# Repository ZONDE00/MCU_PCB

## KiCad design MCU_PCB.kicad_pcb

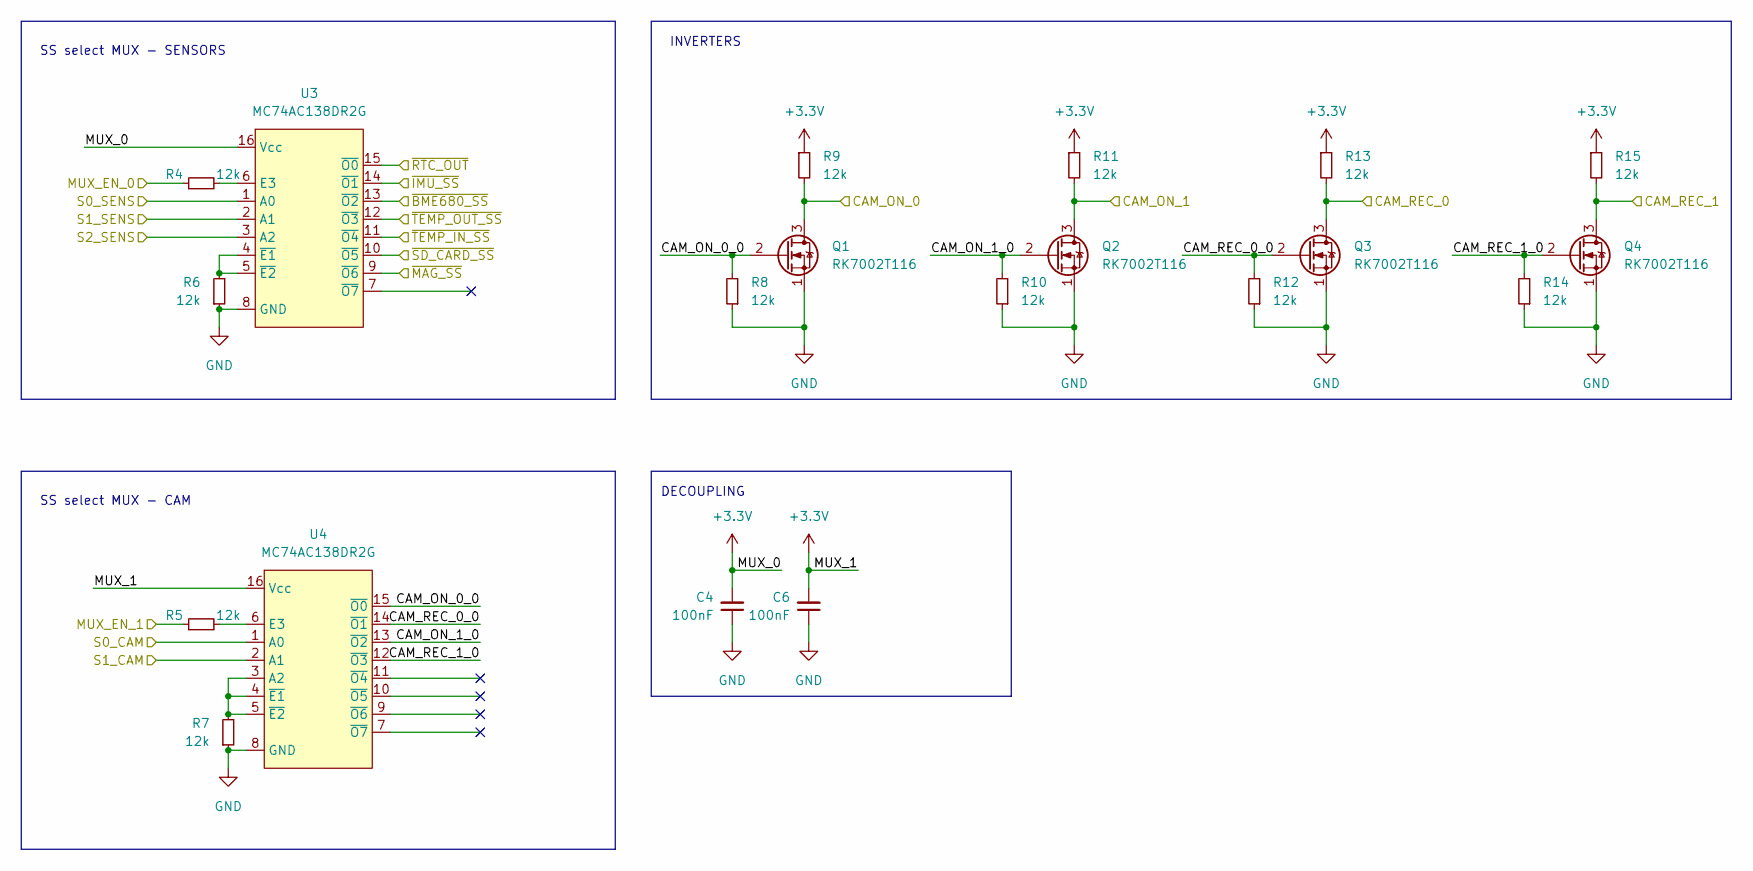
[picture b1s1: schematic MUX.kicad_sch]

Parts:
C4, C6: 100nF; C_0402_1005Metric
Q1, Q2, Q3, Q4: RK7002T116; SOT-23
R4, R5, R6, R7, R8, R9, R10, R11, R12, R13, R14, R15: 12k; R_0402_1005Metric
U3, U4: MC74AC138DR2G; SOIC-16_3.9x9.9mm_P1.27mm

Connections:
+3V3: C4.2, C6.2, R9.1, R11.1, R13.1, R15.1, U3.16 (Vcc), U4.16 (Vcc); also elsewhere on the board
/CAM_SENS/ON/OFF_0: Q1.3 (D), R9.2; also elsewhere on the board
/CAM_SENS/ON/OFF_1: Q2.3 (D), R11.2; also elsewhere on the board
/CAM_SENS/REC_0: Q3.3 (D), R13.2; also elsewhere on the board
/CAM_SENS/REC_1: Q4.3 (D), R15.2; also elsewhere on the board
/CAM_SENS/~BME680_SS: U3.13 (~O2); also elsewhere on the board
/CAM_SENS/~TEMP_OUT_SS: U3.12 (~O3); also elsewhere on the board
/MCU/MUX_EN_0: R4.1; also elsewhere on the board
/MCU/MUX_EN_1: R5.1; also elsewhere on the board
/MCU/S0_CAM: U4.1 (A0); also elsewhere on the board
/MCU/S0_SENS: U3.1 (A0); also elsewhere on the board
/MCU/S1_CAM: U4.2 (A1); also elsewhere on the board
/MCU/S1_SENS: U3.2 (A1); also elsewhere on the board
/MCU/S2_SENS: U3.3 (A2); also elsewhere on the board
/MUX/CAM_ON_0_0: Q1.2 (G), R8.2, U4.15 (~O0)
/MUX/CAM_ON_1_0: Q2.2 (G), R10.2, U4.13 (~O2)
/MUX/CAM_REC_0_0: Q3.2 (G), R12.2, U4.14 (~O1)
/MUX/CAM_REC_1_0: Q4.2 (G), R14.2, U4.12 (~O3)
/MUX/~IMU_SS: U3.14 (~O1); also elsewhere on the board
/MUX/~MAG_SS: U3.9 (~O6); also elsewhere on the board
/MUX/~RTC_OUT: U3.15 (~O0); also elsewhere on the board
/MUX/~SD_CARD_SS: U3.10 (~O5); also elsewhere on the board
/MUX/~TEMP_IN_SS: U3.11 (~O4); also elsewhere on the board
GND: C4.1, C6.1, Q1.1 (S), Q2.1 (S), Q3.1 (S), Q4.1 (S), R6.1, R7.1, R8.1, R10.1, R12.1, R14.1, U3.8 (GND), U4.8 (GND); also elsewhere on the board
unnamed: R4.2, U3.6 (E3)
unnamed: R5.2, U4.6 (E3)
unnamed: R6.2, U3.4 (~E1), U3.5 (~E2)
unnamed: R7.2, U4.3 (A2), U4.4 (~E1), U4.5 (~E2)

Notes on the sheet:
SS select MUX - SENSORS
SS select MUX - CAM
INVERTERS
DECOUPLING

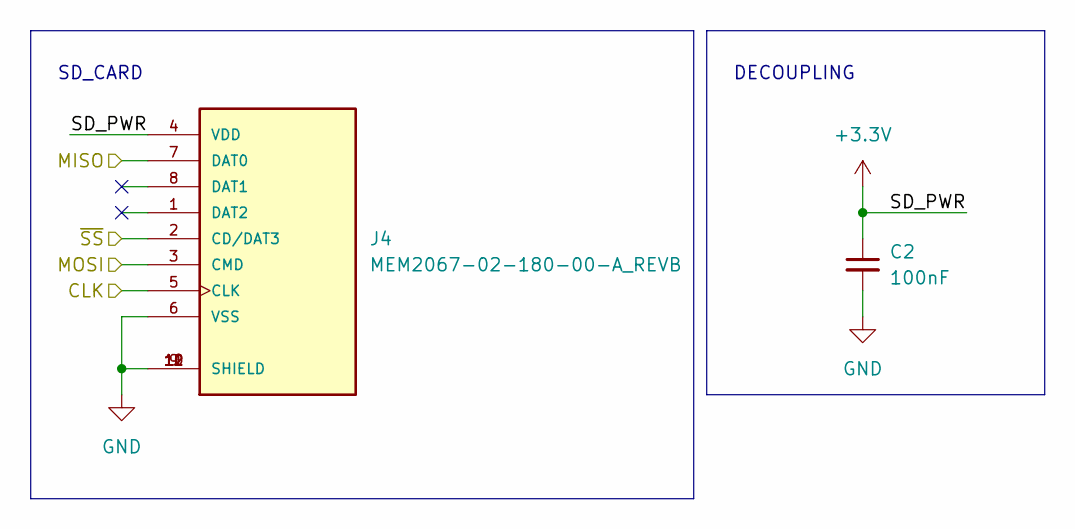
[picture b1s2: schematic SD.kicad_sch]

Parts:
C2: 100nF; C_0402_1005Metric
J4: MEM2067-02-180-00-A_REVB; GCT_MEM2067-02-180-00-A_REVB

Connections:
+3V3: C2.1, J4.4 (VDD); also elsewhere on the board
/CAM_SENS/CLK: J4.5 (CLK); also elsewhere on the board
/CAM_SENS/MISO: J4.7 (DAT0); also elsewhere on the board
/CAM_SENS/MOSI: J4.3 (CMD); also elsewhere on the board
/MUX/~SD_CARD_SS: J4.2 (CD/DAT3); also elsewhere on the board
GND: C2.2, J4.6 (VSS), J4.9 (SHIELD), J4.10 (SHIELD), J4.11 (SHIELD), J4.12 (SHIELD); also elsewhere on the board

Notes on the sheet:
SD_CARD
DECOUPLING

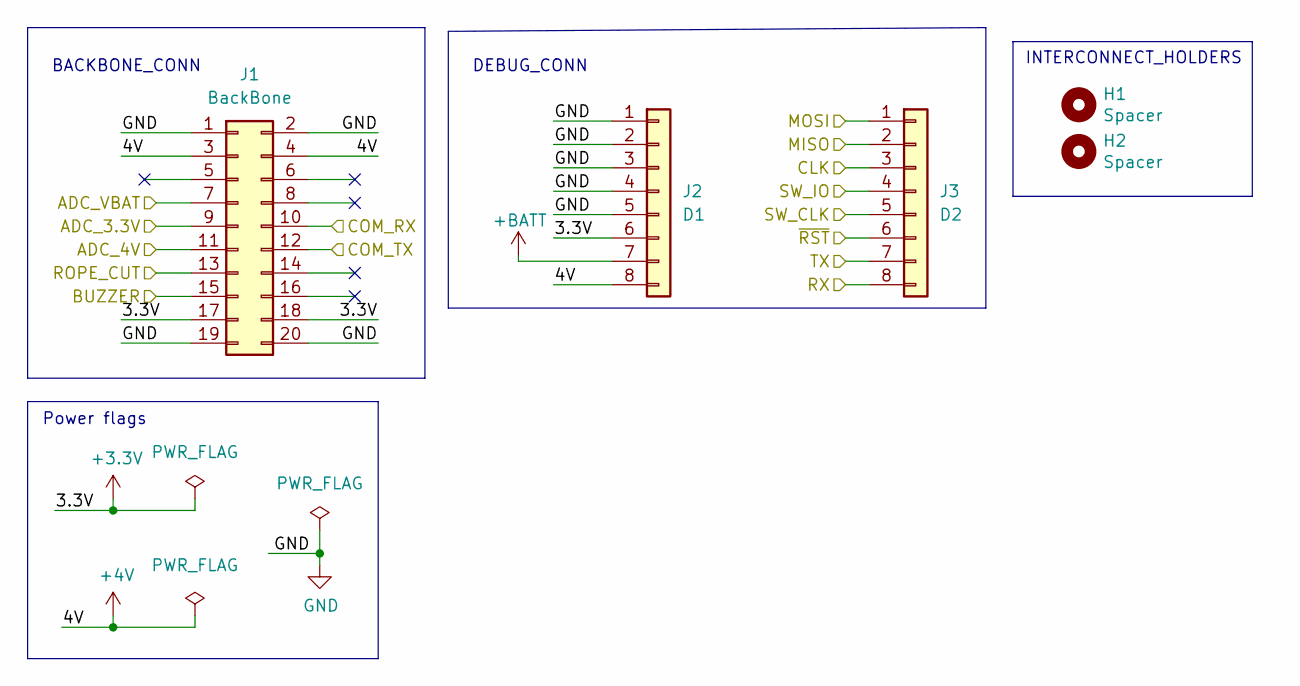
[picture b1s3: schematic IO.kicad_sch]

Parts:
H1, H2: Spacer; MountingHole_3.2mm_M3
J1: BackBone; PinSocket_2x10_P2.54mm_Horizontal
J2: D1; PinSocket_1x08_P2.54mm_Horizontal
J3: D2; PinSocket_1x08_P2.54mm_Horizontal

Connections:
+3V3: J1.17, J1.18, J2.6; also elsewhere on the board
+4V: J1.3, J1.4, J2.8; also elsewhere on the board
+BATT: J2.7; also elsewhere on the board
/CAM_SENS/CLK: J3.3; also elsewhere on the board
/CAM_SENS/MISO: J3.2; also elsewhere on the board
/CAM_SENS/MOSI: J3.1; also elsewhere on the board
/IO/ADC_3.3V: J1.9; also elsewhere on the board
/IO/ADC_4V: J1.11; also elsewhere on the board
/IO/ADC_VBAT: J1.7; also elsewhere on the board
/IO/BUZZER: J1.15; also elsewhere on the board
/IO/COM_RX: J1.10; also elsewhere on the board
/IO/COM_TX: J1.12; also elsewhere on the board
/IO/ROPE_CUT: J1.13; also elsewhere on the board
/IO/RX: J3.8; also elsewhere on the board
/IO/SW_CLK: J3.5; also elsewhere on the board
/IO/SW_IO: J3.4; also elsewhere on the board
/IO/TX: J3.7; also elsewhere on the board
/IO/~RST: J3.6; also elsewhere on the board
GND: J1.1, J1.2, J1.19, J1.20, J2.1, J2.2, J2.3, J2.4, J2.5; also elsewhere on the board

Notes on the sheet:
BACKBONE_CONN
DEBUG_CONN
Power flags
INTERCONNECT_HOLDERS

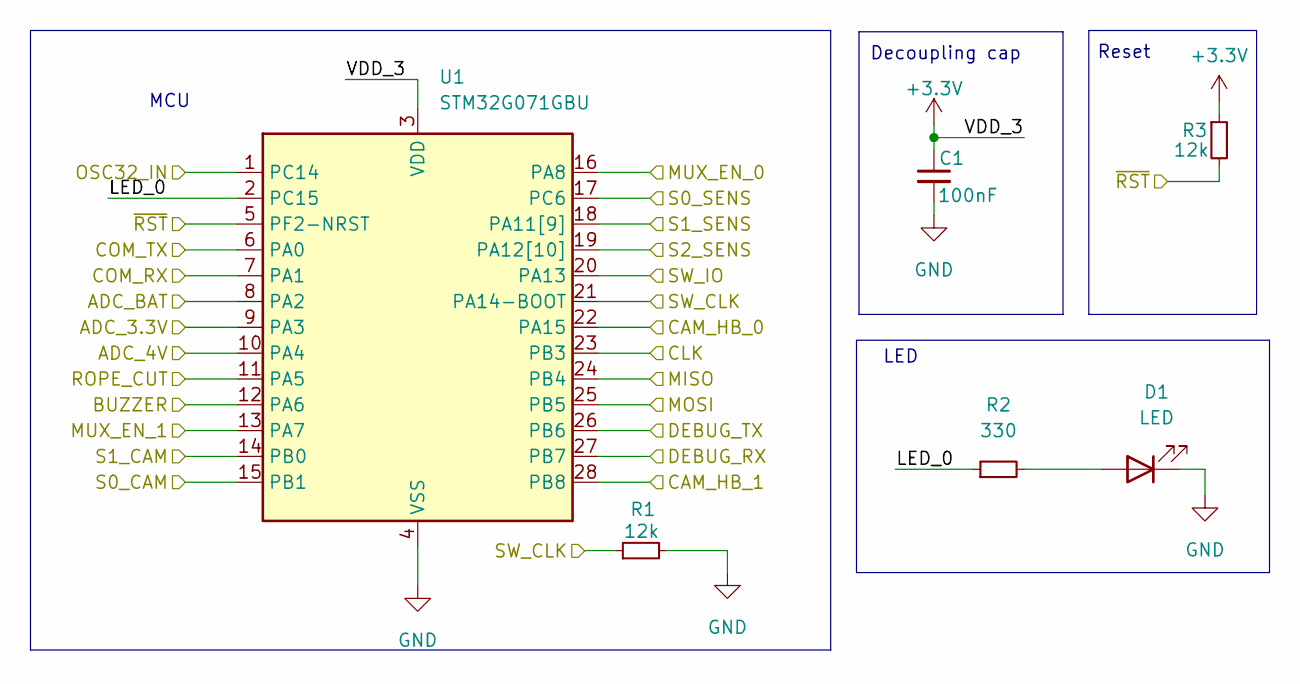
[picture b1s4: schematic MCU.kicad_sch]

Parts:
C1: 100nF; C_0402_1005Metric
D1: LED; LED_0603_1608Metric
R1, R3: 12k; R_0402_1005Metric
R2: 330; R_0402_1005Metric
U1: STM32G071GBU; QFN-28_4x4mm_P0.5mm

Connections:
+3V3: C1.1, R3.1, U1.3 (VDD); also elsewhere on the board
/CAM_SENS/CLK: U1.23 (PB3); also elsewhere on the board
/CAM_SENS/HB_0: U1.22 (PA15); also elsewhere on the board
/CAM_SENS/HB_1: U1.28 (PB8); also elsewhere on the board
/CAM_SENS/MISO: U1.24 (PB4); also elsewhere on the board
/CAM_SENS/MOSI: U1.25 (PB5); also elsewhere on the board
/IO/ADC_3.3V: U1.9 (PA3); also elsewhere on the board
/IO/ADC_4V: U1.10 (PA4); also elsewhere on the board
/IO/ADC_VBAT: U1.8 (PA2); also elsewhere on the board
/IO/BUZZER: U1.12 (PA6); also elsewhere on the board
/IO/COM_RX: U1.7 (PA1); also elsewhere on the board
/IO/COM_TX: U1.6 (PA0); also elsewhere on the board
/IO/ROPE_CUT: U1.11 (PA5); also elsewhere on the board
/IO/RX: U1.27 (PB7); also elsewhere on the board
/IO/SW_CLK: R1.1, U1.21 (PA14-BOOT); also elsewhere on the board
/IO/SW_IO: U1.20 (PA13); also elsewhere on the board
/IO/TX: U1.26 (PB6); also elsewhere on the board
/IO/~RST: R3.2, U1.5 (PF2-NRST); also elsewhere on the board
/MCU/LED_0: R2.1, U1.2 (PC15)
/MCU/MUX_EN_0: U1.16 (PA8); also elsewhere on the board
/MCU/MUX_EN_1: U1.13 (PA7); also elsewhere on the board
/MCU/OSC32_IN: U1.1 (PC14); also elsewhere on the board
/MCU/S0_CAM: U1.15 (PB1); also elsewhere on the board
/MCU/S0_SENS: U1.17 (PC6); also elsewhere on the board
/MCU/S1_CAM: U1.14 (PB0); also elsewhere on the board
/MCU/S1_SENS: U1.18 (PA11[9]); also elsewhere on the board
/MCU/S2_SENS: U1.19 (PA12[10]); also elsewhere on the board
GND: C1.2, D1.1 (K), R1.2, U1.4 (VSS); also elsewhere on the board
unnamed: D1.2 (A), R2.2

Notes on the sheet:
Reset
MCU
Decoupling cap
LED

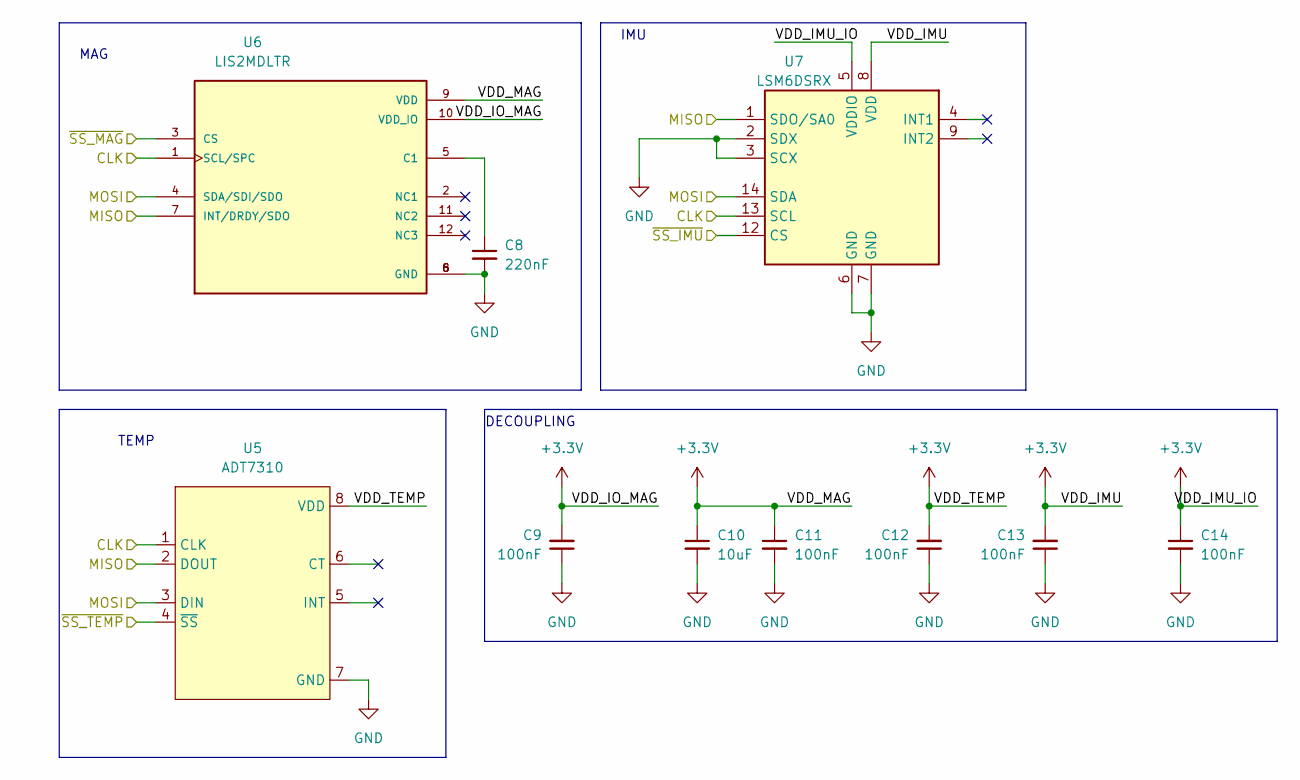
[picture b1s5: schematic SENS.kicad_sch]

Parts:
C8: 220nF; C_0402_1005Metric
C9, C11, C12, C13, C14: 100nF; C_0402_1005Metric
C10: 10uF; C_0402_1005Metric
U5: ADT7310; SOIC-8_3.9x4.9mm_P1.27mm
U6: LIS2MDLTR; PQFN50P200X200X70-12N; PARTREV Rev 5
U7: LSM6DSRX; LGA-14_3x2.5mm_P0.5mm_LayoutBorder3x4y

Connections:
+3V3: C9.2, C10.1, C11.1, C12.2, C13.2, C14.1, U5.8 (VDD), U6.9 (VDD), U6.10 (VDD_IO), U7.5 (VDDIO), U7.8 (VDD); also elsewhere on the board
/CAM_SENS/CLK: U5.1 (CLK), U6.1 (SCL/SPC), U7.13 (SCL); also elsewhere on the board
/CAM_SENS/MISO: U5.2 (DOUT), U6.7 (INT/DRDY/SDO), U7.1 (SDO/SA0); also elsewhere on the board
/CAM_SENS/MOSI: U5.3 (DIN), U6.4 (SDA/SDI/SDO), U7.14 (SDA); also elsewhere on the board
/MUX/~IMU_SS: U7.12 (CS); also elsewhere on the board
/MUX/~MAG_SS: U6.3 (CS); also elsewhere on the board
/MUX/~TEMP_IN_SS: U5.4 (~SS); also elsewhere on the board
GND: C8.2, C9.1, C10.2, C11.2, C12.1, C13.1, C14.2, U5.7 (GND), U6.6 (GND), U6.8 (GND), U7.2 (SDX), U7.3 (SCX), U7.6 (GND), U7.7 (GND); also elsewhere on the board
unnamed: C8.1, U6.5 (C1)

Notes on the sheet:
MAG
DECOUPLING
IMU
TEMP

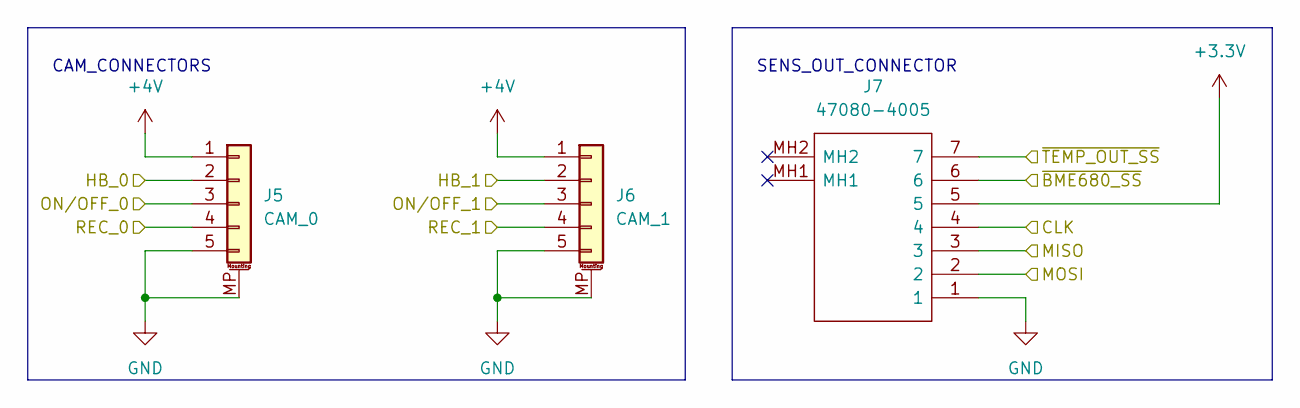
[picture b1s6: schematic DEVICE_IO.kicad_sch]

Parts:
J5: CAM_0; JST_SH_BM05B-SRSS-TB_1x05-1MP_P1.00mm_Vertical
J6: CAM_1; JST_SH_BM05B-SRSS-TB_1x05-1MP_P1.00mm_Vertical
J7: 47080-4005; 470804005; Mouser Part Number 538-47080-4005

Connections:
+3V3: J7.5; also elsewhere on the board
+4V: J5.1, J6.1; also elsewhere on the board
/CAM_SENS/CLK: J7.4; also elsewhere on the board
/CAM_SENS/HB_0: J5.2; also elsewhere on the board
/CAM_SENS/HB_1: J6.2; also elsewhere on the board
/CAM_SENS/MISO: J7.3; also elsewhere on the board
/CAM_SENS/MOSI: J7.2; also elsewhere on the board
/CAM_SENS/ON/OFF_0: J5.3; also elsewhere on the board
/CAM_SENS/ON/OFF_1: J6.3; also elsewhere on the board
/CAM_SENS/REC_0: J5.4; also elsewhere on the board
/CAM_SENS/REC_1: J6.4; also elsewhere on the board
/CAM_SENS/~BME680_SS: J7.6; also elsewhere on the board
/CAM_SENS/~TEMP_OUT_SS: J7.7; also elsewhere on the board
GND: J5.5, J5.MP (MountPin), J6.5, J6.MP (MountPin), J7.1; also elsewhere on the board

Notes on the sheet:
CAM_CONNECTORS
SENS_OUT_CONNECTOR

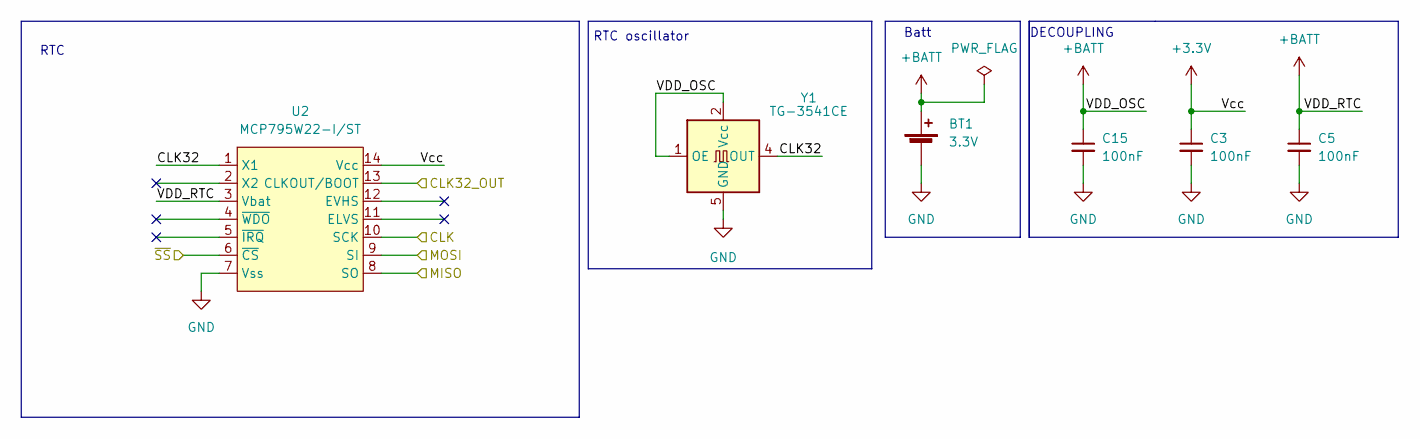
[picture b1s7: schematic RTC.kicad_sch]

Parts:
BT1: 3.3V; 3034
C3, C5, C15: 100nF; C_0402_1005Metric
U2: MCP795W22-I/ST; TSSOP-14_4.4x5mm_P0.65mm
Y1: TG-3541CE; Oscillator_SMD_SeikoEpson_TG-3541CE_3.2x2.5mm

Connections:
+3V3: C3.1, U2.14 (Vcc); also elsewhere on the board
+BATT: BT1.1 (+), C5.1, C15.1, U2.3 (Vbat), Y1.1 (OE), Y1.2 (Vcc), Y1.3 (Vcc); also elsewhere on the board
/CAM_SENS/CLK: U2.10 (SCK); also elsewhere on the board
/CAM_SENS/MISO: U2.8 (SO); also elsewhere on the board
/CAM_SENS/MOSI: U2.9 (SI); also elsewhere on the board
/MCU/OSC32_IN: U2.13 (CLKOUT/BOOT); also elsewhere on the board
/MUX/~RTC_OUT: U2.6 (~CS); also elsewhere on the board
/RTC/CLK32: U2.1 (X1), Y1.4 (OUT)
GND: BT1.2 (-), C3.2, C5.2, C15.2, U2.7 (Vss), Y1.5 (GND), Y1.7 (GND), Y1.8 (GND), Y1.9 (GND); also elsewhere on the board

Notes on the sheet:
RTC
RTC oscillator
DECOUPLING
Batt

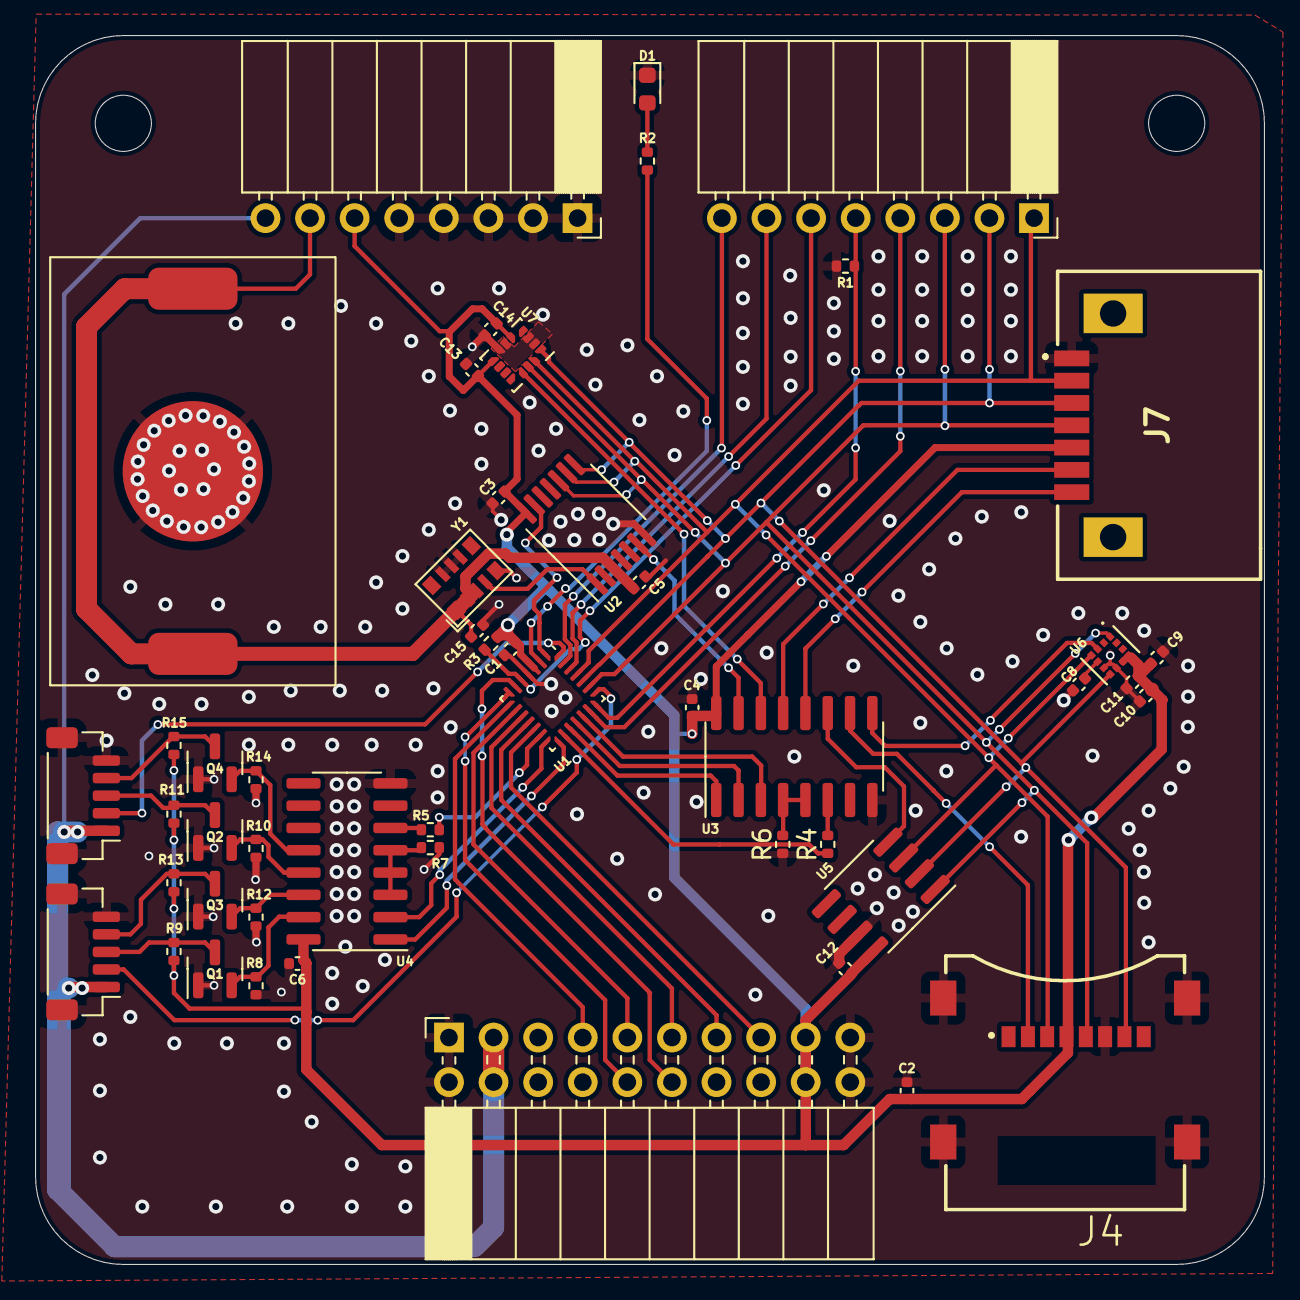
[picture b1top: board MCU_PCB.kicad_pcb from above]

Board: 2 copper layers, 70.0 x 70.0 mm, 52 parts (0 on the bottom side), 52 nets.

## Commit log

2022-09-25 unfinished version 0.1v
    Only schematics
2022-11-19 0.1v MCU KiCad
    Aesthetics needs to be improved.
    Trace width needs to be changed.
    More sufficient grounding.
    Component placement could be changed.
2022-11-20 0.1v finished KiCad
    Aesthetics needs improving;
    Component placement can be changed;
    More sufficient grounding is necessary.
    SATA connector pinouts has been changed;
    Microcontroller pinouts has been changed - to make tracing easier.
2022-11-20 0.2v KiCad
    Improved aesthetics;
    More sufficient grounding.
    What have to be done:
    Traces have to be moved closer and some of the trace widths have to be changed from 0.2 mm to 0.25 mm (especially MCU).
2022-11-22 Changed DE-MUX and logic behind it.
2022-11-23 0.3v KiCad
    Needs improvements:
    -Visual
    -Better grounding
    -Component placement
2022-11-23 0.3V KiCad Final version
2022-12-13 V1
    - Corrected SD-cards footprint and schematical represantation;
    - Corrected RTC shematics:
    - changed oscilators power supply from internal 3v3 to Vbat so RTC works when PCB is disconnected from external power supply [PWR PCB];
    - 32 kHz to microcontroller now comes from RTC module;
    - added 100 nF decoupling capacitor to Vbat RTC pin.
    - Corrected couple connections and component placement on PCB
